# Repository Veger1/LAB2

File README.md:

Alignment tool
==============
Download Main.exe from the latest release. 
Opening Main.exe may open console depending on version, then the application will start.

Known issues:
v1.3.0 and below:
- Loading in a dataset with an existing name and pressing 'cancel' still produces an empty dataset.
- Save button can produce empty .csv files.

v1.2.0 and below:
- The label for dataset names is limited in size, so long dataset names will be cut off.
- Though it is possible to acquire encoder data with the arduino code, the application cannot yet switch to this mode.
- Sampler will often not work with 'ignore limits' on OFF

v1.1.0 and below:
- Loading a csv file which contains a dataset name which is already in use will cause the dataset not be loaded.

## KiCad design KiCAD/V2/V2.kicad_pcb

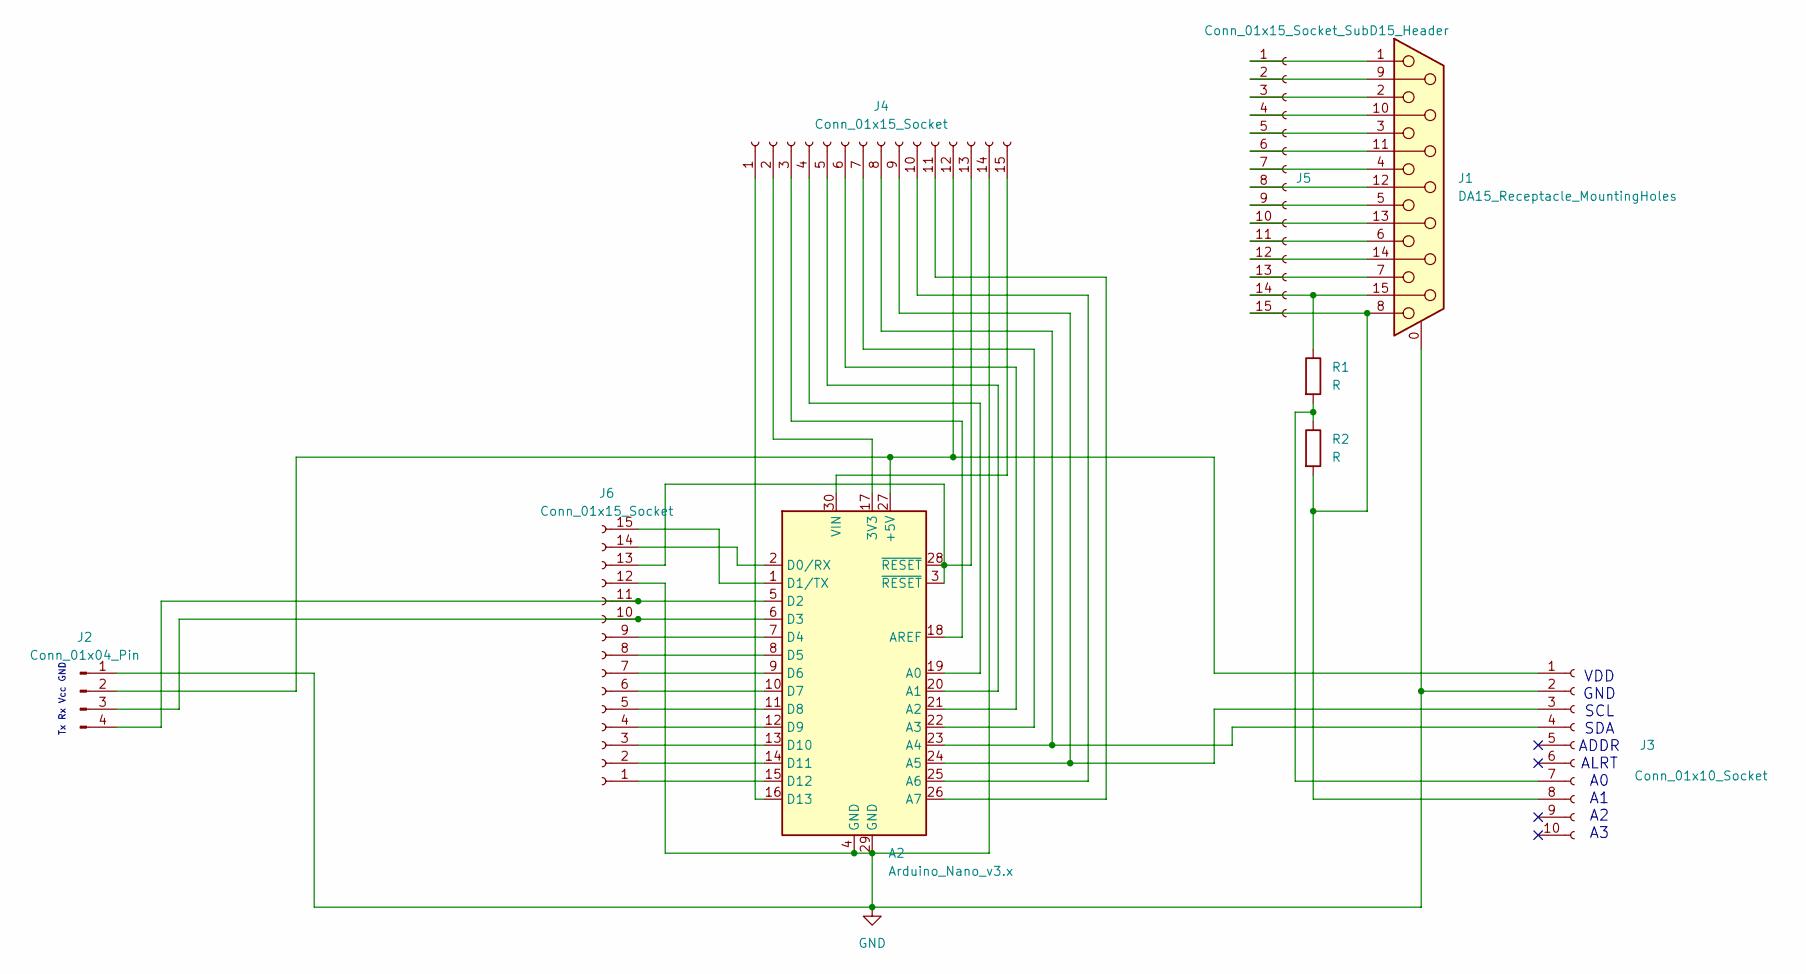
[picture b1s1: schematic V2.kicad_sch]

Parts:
A2: Arduino_Nano_v3.x; Arduino_Nano
J1: DA15_Receptacle_MountingHoles; DSUB-15_Female_Horizontal_P2.77x2.84mm_EdgePinOffset9.90mm_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
J2: Conn_01x04_Pin; PinHeader_1x04_P2.54mm_Horizontal
J3: Conn_01x10_Socket; PinSocket_1x10_P2.54mm_Vertical
J4, J6: Conn_01x15_Socket; PinSocket_1x15_P2.54mm_Vertical
J5: Conn_01x15_Socket_SubD15_Header; PinSocket_1x15_P2.54mm_Vertical
R1, R2: R; R_Axial_DIN0207_L6.3mm_D2.5mm_P7.62mm_Horizontal

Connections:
GND: A2.4 (GND), A2.29 (GND), J1.0 (PAD), J2.1, J3.2, J4.14, J6.12
unnamed: A2.17 (3V3), J4.2
unnamed: A2.27 (+5V), J2.2, J3.1, J4.12
unnamed: A2.19 (A0), J4.4
unnamed: A2.20 (A1), J4.5
unnamed: A2.21 (A2), J4.6
unnamed: A2.22 (A3), J4.7
unnamed: A2.23 (A4), J3.4, J4.8
unnamed: A2.24 (A5), J3.3, J4.9
unnamed: A2.25 (A6), J4.10
unnamed: A2.26 (A7), J4.11
unnamed: A2.18 (AREF), J4.3
unnamed: A2.2 (D0/RX), J6.14
unnamed: A2.1 (D1/TX), J6.15
unnamed: A2.5 (D2), J2.4, J6.11
unnamed: A2.6 (D3), J2.3, J6.10
unnamed: A2.7 (D4), J6.9
unnamed: A2.8 (D5), J6.8
unnamed: A2.9 (D6), J6.7
unnamed: A2.10 (D7), J6.6
unnamed: A2.11 (D8), J6.5
unnamed: A2.12 (D9), J6.4
unnamed: A2.13 (D10), J6.3
unnamed: A2.14 (D11), J6.2
unnamed: A2.15 (D12), J6.1
unnamed: A2.16 (D13), J4.1
unnamed: A2.30 (VIN), J4.15
unnamed: J1.9, J5.2
unnamed: J1.10, J5.4
unnamed: J1.12, J5.8
unnamed: J1.13, J5.10
unnamed: J1.14, J5.12
unnamed: J1.15, J5.14, R1.1
unnamed: J1.11 (P111), J5.6
unnamed: J3.7, R1.2, R2.1
unnamed: J1.8, J3.8, J5.15, R2.2
unnamed: A2.3 (~RESET), A2.28 (~RESET), J4.13, J6.13
unnamed: J1.1, J5.1
unnamed: J1.2, J5.3
unnamed: J1.3, J5.5
unnamed: J1.4, J5.7
unnamed: J1.5, J5.9
unnamed: J1.6, J5.11
unnamed: J1.7, J5.13

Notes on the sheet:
Tx Rx Vcc GND
VDD GND SCL SDA ADDR ALRT A0 A1 A2 A3

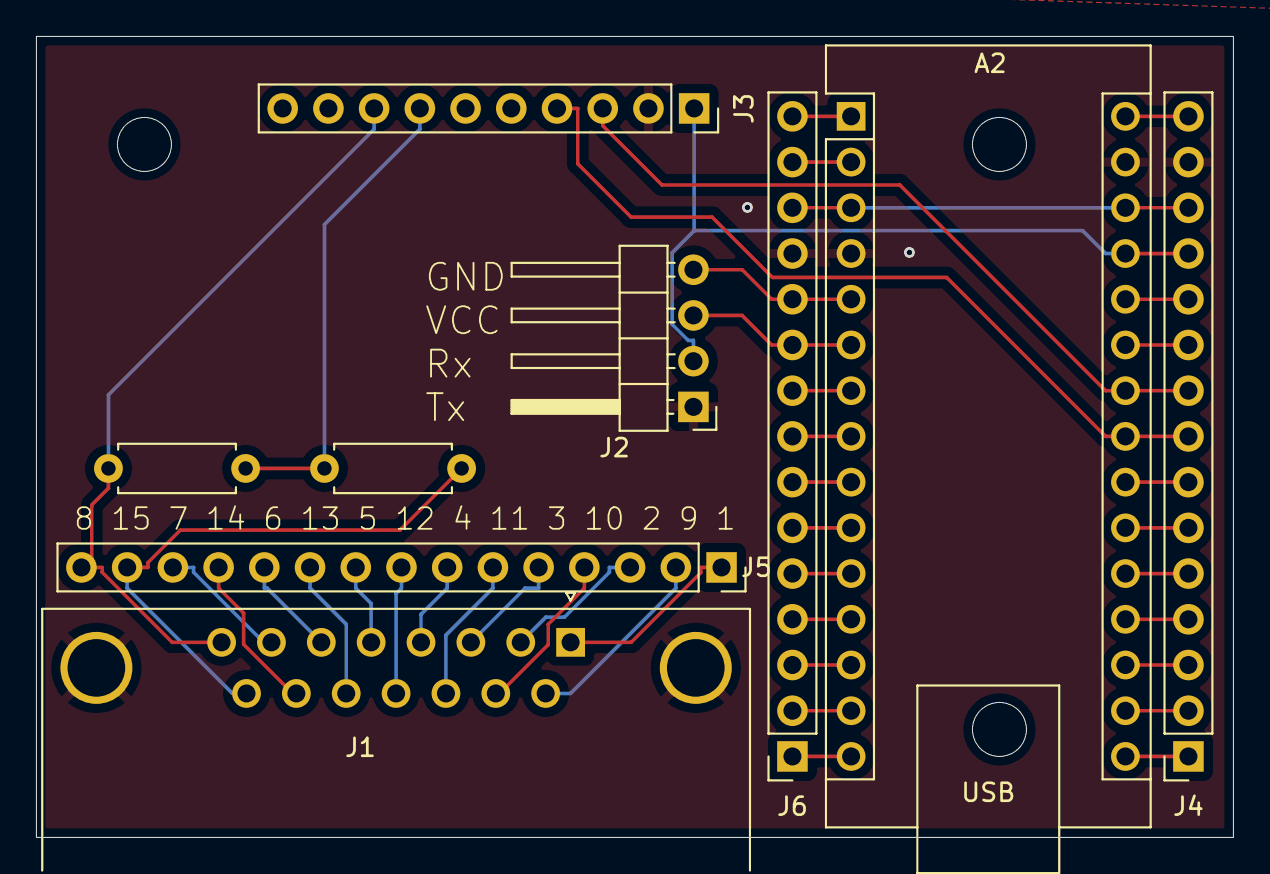
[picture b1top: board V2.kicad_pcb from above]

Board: 2 copper layers, 66.5 x 44.5 mm, 9 parts (0 on the bottom side), 44 nets.

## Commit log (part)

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2024-09-03 Base
2024-09-03 GUI updates 1
2024-09-04 Stop tracking worksapce.xml
2024-09-04 X-limits
2024-09-05 Pre threading fix
2024-09-05 GUI data stretch, aligning
2024-09-06 Measurement report generation
2024-09-06 Add Arduino file
2024-09-06 KiCAD files
2024-11-15 Copy
2024-11-21 Comments
2024-11-21 Functions separation
2024-11-22 Sampler
2024-11-29 29/11
2024-11-29 Added executable
2024-12-05 Plotting rework, trendlines
2024-12-05 Added offline sampler
2024-12-05 Changed plotting and de-trending data
2024-12-05 Updated known issues
2024-12-06 Added ignore limits
2024-12-06 Updated MANUAL/TODO
2024-12-06 Added tooltip class
2024-12-06 Enabled terminal
2024-12-06 Arduino code
2024-12-11 Removed ignore limits
2024-12-11 Added legend toggle
2024-12-11 Fixed report, added PNG, moved plot
2024-12-11 Re-organised
